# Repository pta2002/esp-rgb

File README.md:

# ESP RGB
An ESP8266-based RGB strip controller

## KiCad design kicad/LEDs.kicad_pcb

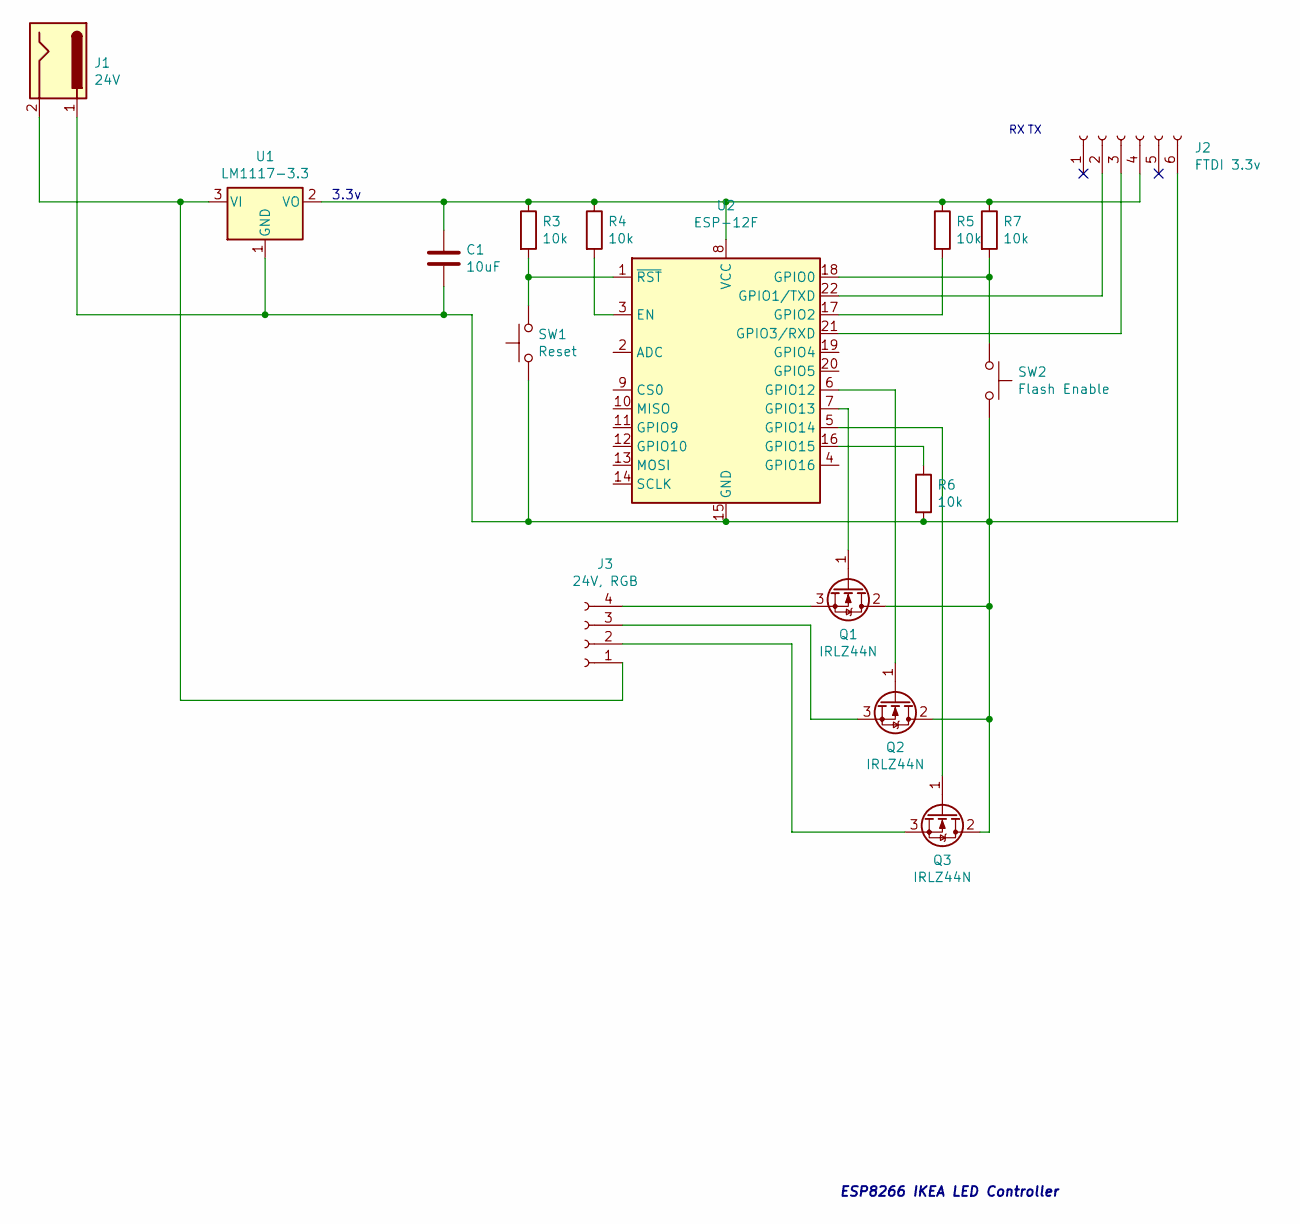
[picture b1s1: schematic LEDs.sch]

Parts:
C1: 10uF; C_0805_2012Metric_Pad1.15x1.40mm_HandSolder
J1: 24V; SolderWire-0.75sqmm_1x02_P7mm_D1.25mm_OD3.5mm
J2: FTDI 3.3v; PinSocket_1x06_P2.54mm_Vertical
J3: 24V, RGB; SolderWire-0.75sqmm_1x04_P7mm_D1.25mm_OD3.5mm
Q1, Q2, Q3: IRLZ44N; TO-220-3_Vertical
R3, R4, R5, R6, R7: 10k; R_0805_2012Metric_Pad1.15x1.40mm_HandSolder
SW1: Reset; SW_SPST_B3U-1000P
SW2: Flash Enable; SW_SPST_B3U-1000P
U1: LM1117-3.3; SOT-223-3_TabPin2
U2: ESP-12F; ESP-12E

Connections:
unnamed: C1.1, J2.4, R3.1, R4.1, R5.1, R7.1, U1.2 (VO), U2.8 (VCC)
unnamed: C1.2, J1.1, J2.6, Q1.2 (D), Q2.2 (D), Q3.2 (D), R6.2, SW1.1, SW2.2, U1.1 (GND), U2.15 (GND)
unnamed: J1.2, J3.1, U1.3 (VI)
unnamed: J2.2, U2.22 (GPIO1/TXD)
unnamed: J2.3, U2.21 (GPIO3/RXD)
unnamed: J3.2, Q3.3 (S)
unnamed: J3.3, Q2.3 (S)
unnamed: J3.4, Q1.3 (S)
unnamed: Q1.1 (G), U2.7 (GPIO13)
unnamed: Q2.1 (G), U2.6 (GPIO12)
unnamed: Q3.1 (G), U2.5 (GPIO14)
unnamed: R3.2, SW1.2, U2.1 (~RST)
unnamed: R4.2, U2.3 (EN)
unnamed: R5.2, U2.17 (GPIO2)
unnamed: R6.1, U2.16 (GPIO15)
unnamed: R7.2, SW2.1, U2.18 (GPIO0)

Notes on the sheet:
3.3v
ESP8266 IKEA LED Controller

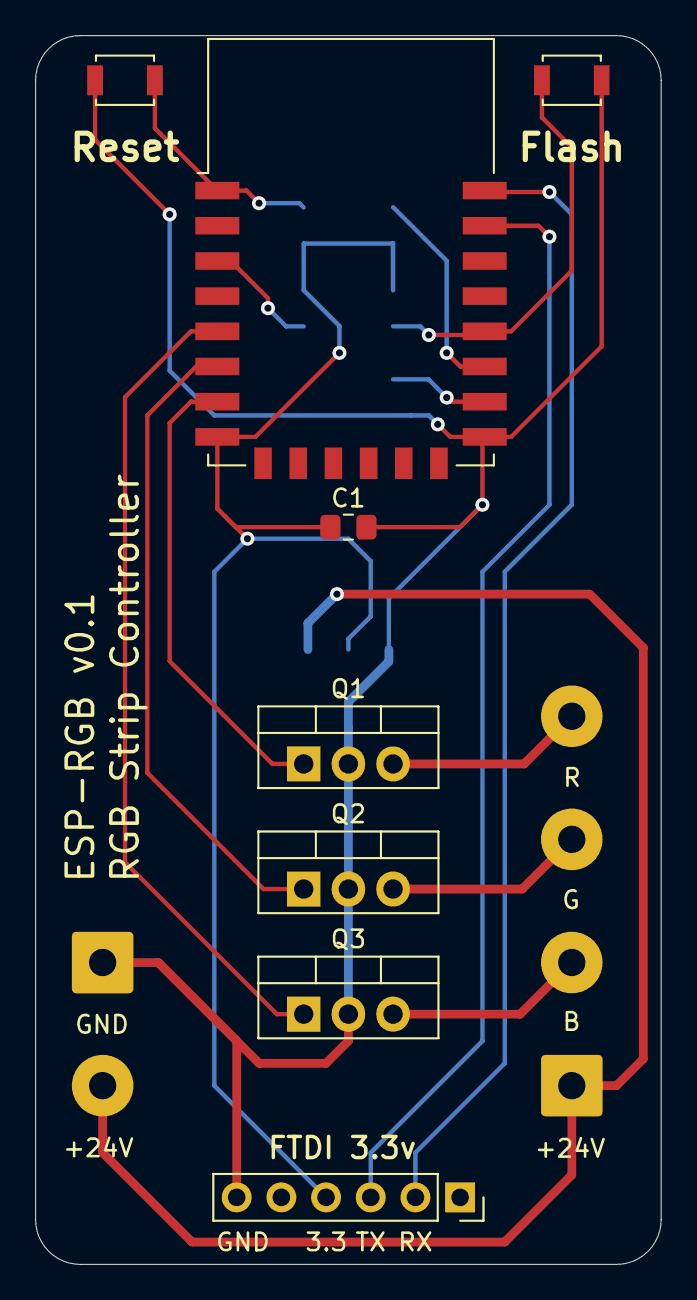
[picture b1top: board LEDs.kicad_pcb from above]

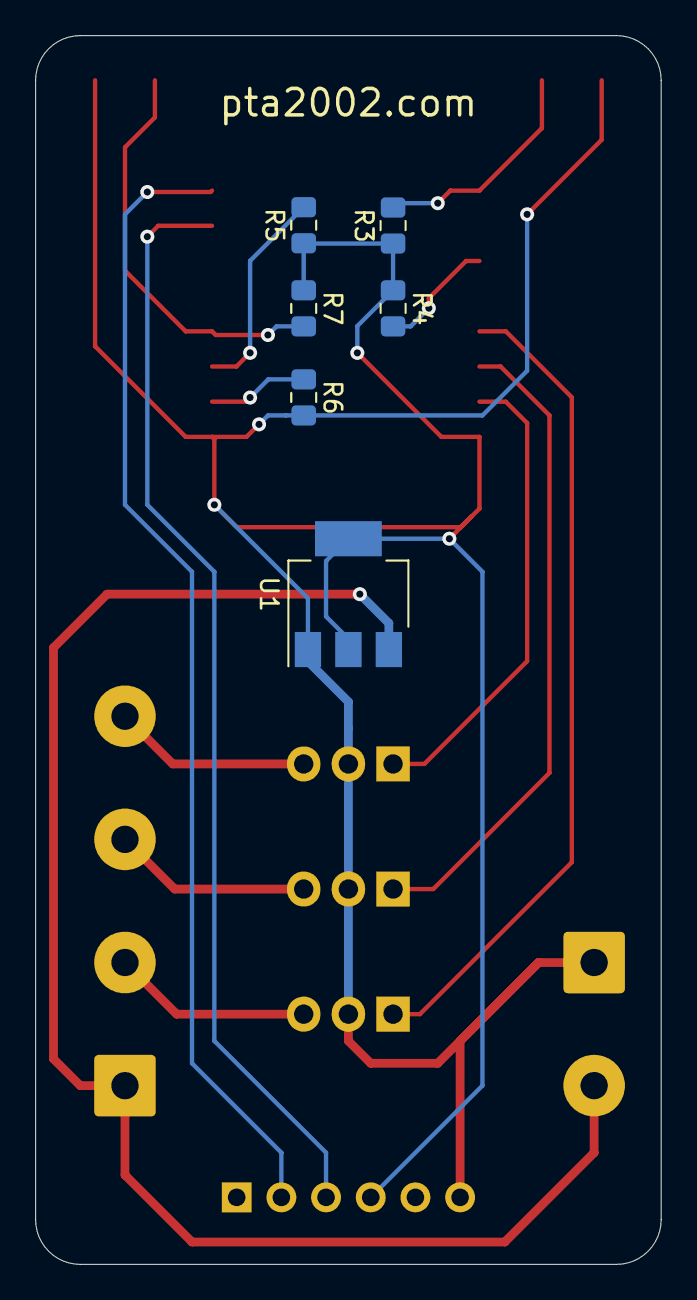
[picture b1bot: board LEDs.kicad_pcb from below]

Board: 2 copper layers, 35.6 x 69.9 mm, 16 parts (6 on the bottom side), 16 nets.

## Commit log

2020-11-24 More organized board
2020-11-25 Organize kicad
